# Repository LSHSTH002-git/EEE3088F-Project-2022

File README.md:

# EEE3088F_2022: GROUP 15 LIGHT SENSOR HAT PROJECT

In this guide we will learn to use the LIGHT SENSOR HAT that is used to detect environmental changes and then set off an alarm to alert the onwner about the changes.

This Sensor is primarily designed for farmers that want to monitor their live stock and prevent thieves from stealing them.

# What you will need
1. You will need an STM32f0discovery board

2. Li-Ion battery

3. jumpers

4.  Laptop

5. Micro usb type B male connector

6. STM32CubeIDE

7. Mini USB type A cable

8. The HAT code

9. The HAT pcb Board

# Setting up the System

Insert the Li-ion battery to the battery holder
connect the STM32f0discovery board to your laptop using the Mini USB type A cable
connect the light sensor HAT to your Laptop using Micro usb type B male connector and you should see two LED's light up
run the HAT code on your pc using STM32CubeIDE 
if you cover up the Light sensor HAT, the Blue LED on the STM32f0discovery board should blink

if you stop covering the Light sensor HAT the blue LED should stop blinking.

# License
[Creative Commons Attribution 4.0 International license](https://choosealicense.com/licenses/cc-by-4.0/)

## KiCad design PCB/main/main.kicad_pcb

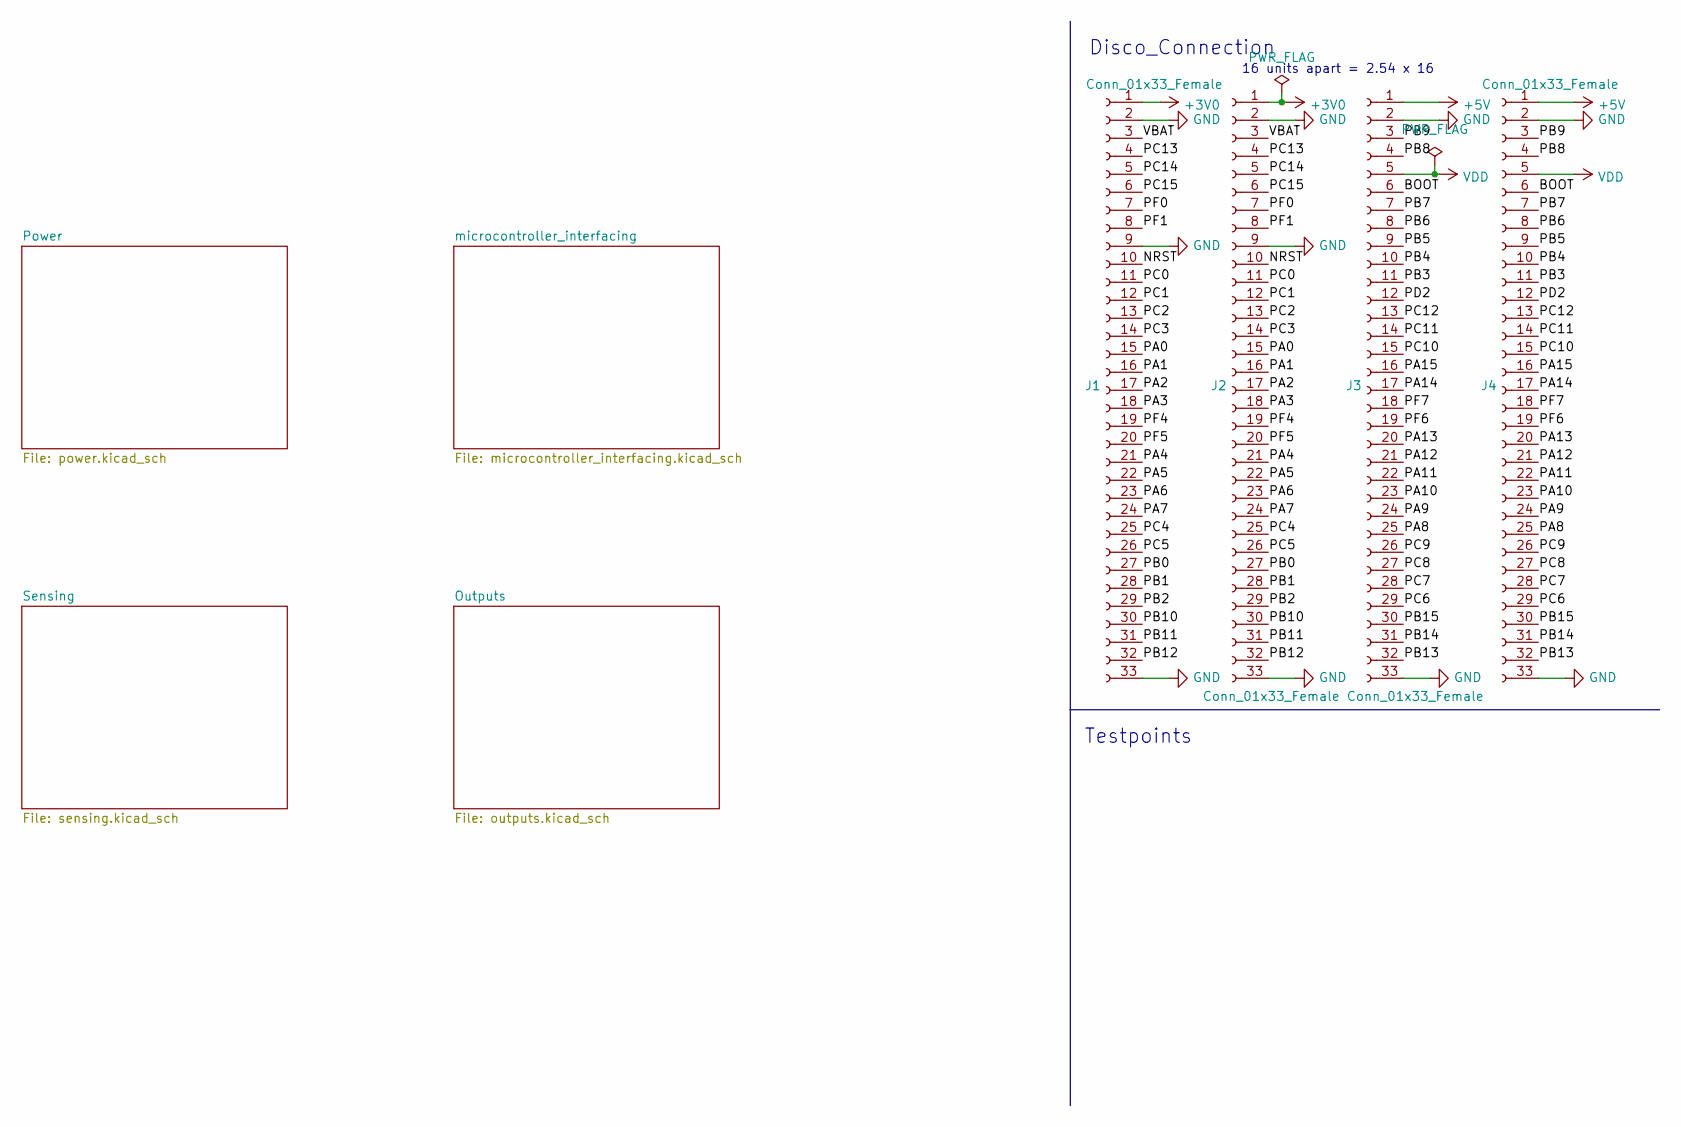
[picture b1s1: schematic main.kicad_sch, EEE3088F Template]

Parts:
J1, J4: Conn_01x33_Female; PinHeader_1x33_P2.54mm_Vertical
J2, J3: Conn_01x33_Female; PinSocket_1x33_P2.54mm_Vertical

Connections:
5V USB: J3.1, J4.1; also elsewhere on the board
+3V0: J1.1, J2.1
/BOOT: J3.6, J4.6
/NRST: J1.10, J2.10
/PA0: J1.15, J2.15
/PA1: J1.16, J2.16
/PA2: J1.17, J2.17
/PA3: J1.18, J2.18
/PA4: J1.21, J2.21
/PA5: J1.22, J2.22
/PA6: J1.23, J2.23
/PA7: J1.24, J2.24
/PA8: J3.25, J4.25
/PA9: J3.24, J4.24
/PA10: J3.23, J4.23
/PA11: J3.22, J4.22
/PA12: J3.21, J4.21
/PA13: J3.20, J4.20
/PA14: J3.17, J4.17
/PA15: J3.16, J4.16
/PB0: J1.27, J2.27
/PB1: J1.28, J2.28
/PB2: J1.29, J2.29
/PB3: J3.11, J4.11
/PB4: J3.10, J4.10
/PB5: J3.9, J4.9
/PB6: J3.8, J4.8
/PB7: J3.7, J4.7
/PB8: J3.4, J4.4
/PB9: J3.3, J4.3
/PB10: J1.30, J2.30
/PB11: J1.31, J2.31
/PB12: J1.32, J2.32
/PB13: J3.32, J4.32
/PB14: J3.31, J4.31
/PB15: J3.30, J4.30
/PC0: J1.11, J2.11
/PC1: J1.12, J2.12
/PC2: J1.13, J2.13
/PC3: J1.14, J2.14
/PC4: J1.25, J2.25
/PC5: J1.26, J2.26
/PC6: J3.29, J4.29
/PC7: J3.28, J4.28
/PC8: J3.27, J4.27
/PC9: J3.26, J4.26
/PC10: J3.15, J4.15
/PC11: J3.14, J4.14
/PC12: J3.13, J4.13
/PC13: J1.4, J2.4
/PC14: J1.5, J2.5
/PC15: J1.6, J2.6
/PD2: J3.12, J4.12
/PF0: J1.7, J2.7
/PF1: J1.8, J2.8
/PF4: J1.19, J2.19
/PF5: J1.20, J2.20
/PF6: J3.19, J4.19
/PF7: J3.18, J4.18
/VBAT: J1.3, J2.3
GND: J1.2, J1.9, J1.33, J2.2, J2.9, J2.33, J3.2, J3.33, J4.2, J4.33; also elsewhere on the board
VDD: J3.5, J4.5

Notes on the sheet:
16 units apart = 2.54 x 16
Disco_Connection
Testpoints

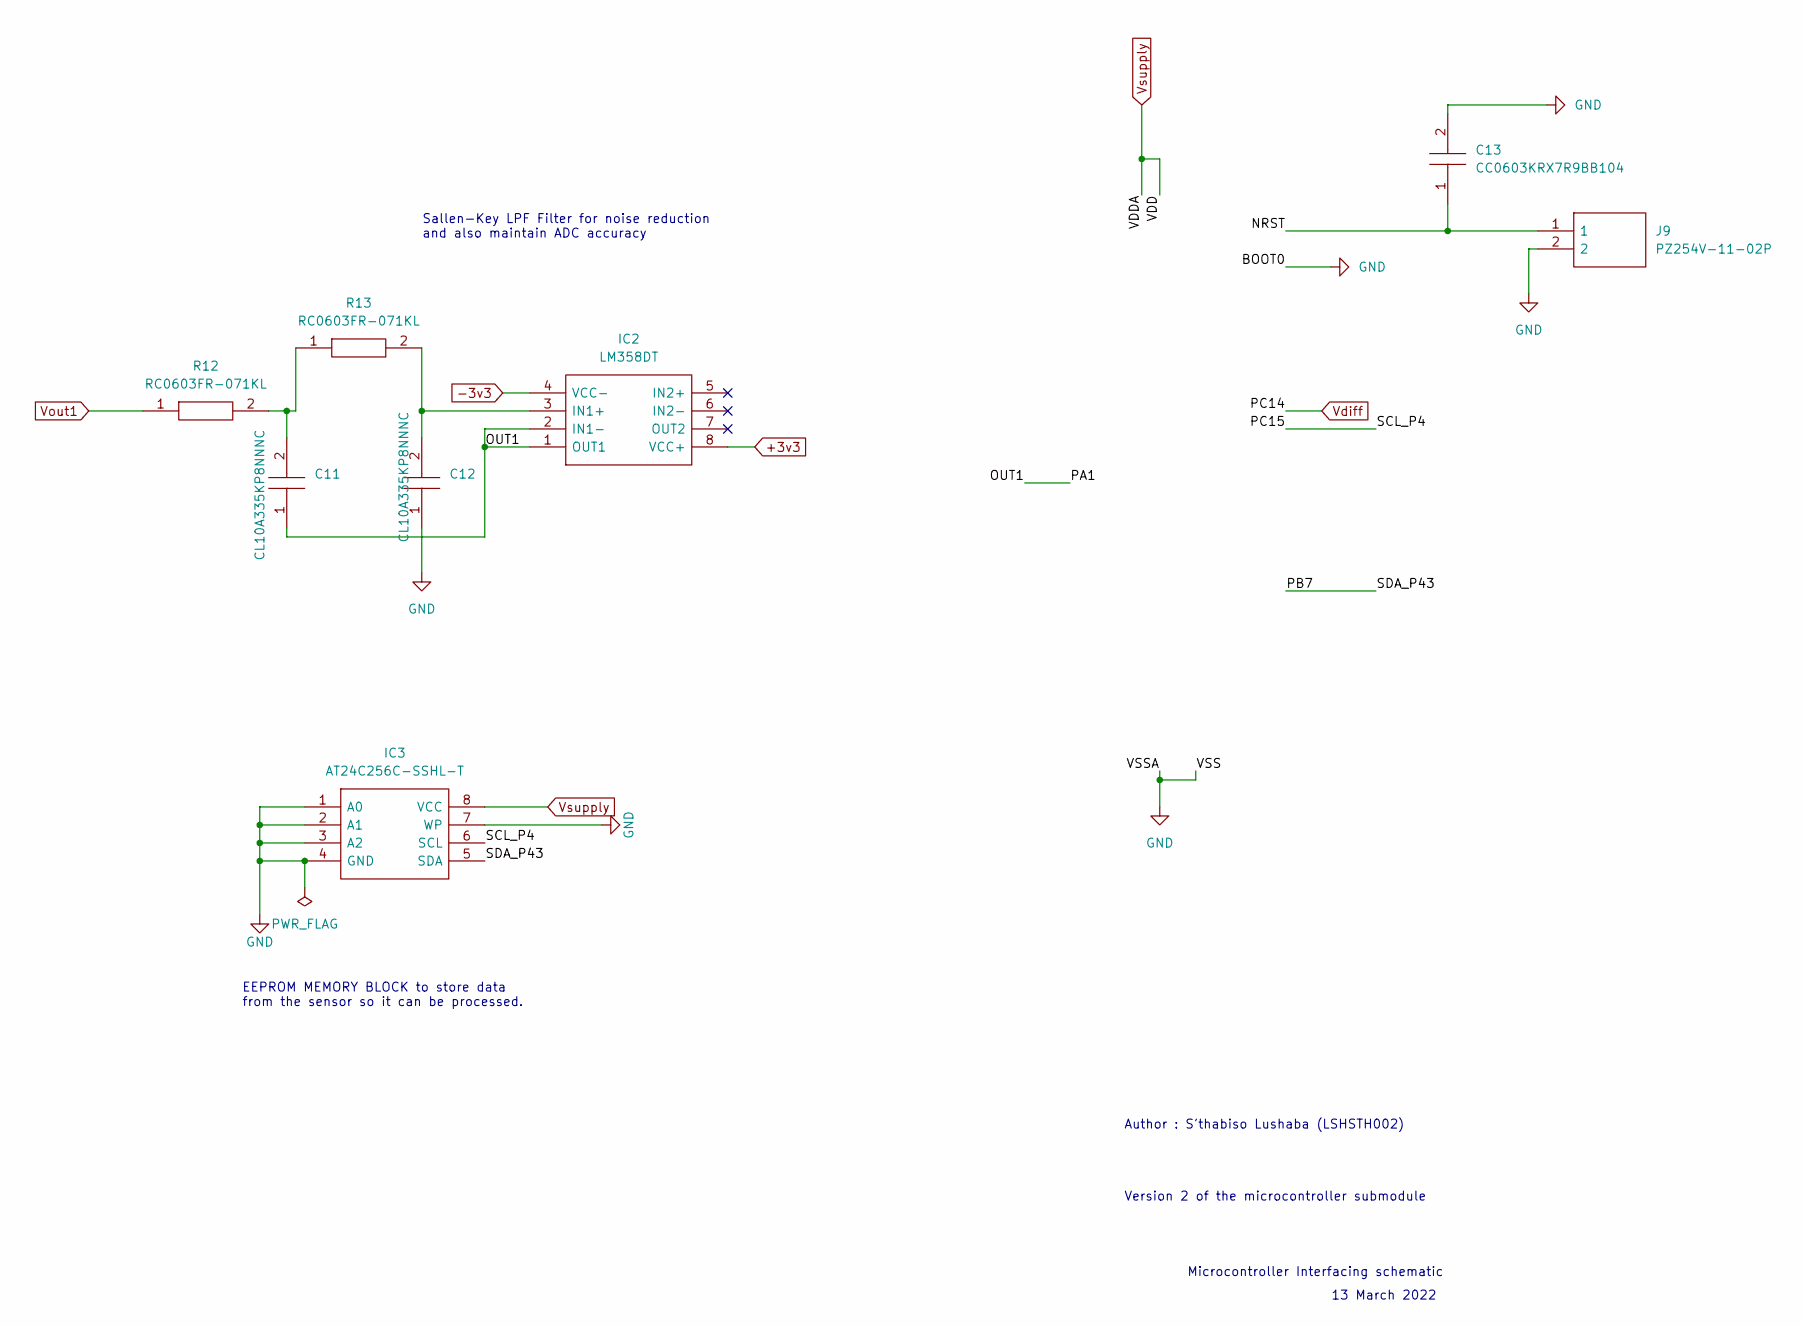
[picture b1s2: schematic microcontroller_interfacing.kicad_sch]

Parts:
C11, C12: CL10A335KP8NNNC; CAPC1608X90N; Manufacturer_Part_Number CL10A335KP8NNNC; Mouser Part Number N/A
C13: CC0603KRX7R9BB104; CAPC1608X90N; Manufacturer_Part_Number CC0603KRX7R9BB104; Mouser Part Number 603-CC603KRX7R9BB104
IC2: LM358DT; SOIC127P600X175-8N; Manufacturer_Part_Number LM358DT; Mouser Part Number 511-LM358DT
IC3: AT24C256C-SSHL-T; SOIC127P600X175-8N; Manufacturer_Part_Number AT24C256C-SSHL-T; Mouser Part Number 556-AT24C256C-SSHL-T
J9: PZ254V-11-02P; HDRV2W64P0X254_1X2_508X250X873P; Manufacturer_Part_Number PZ254V-11-02P; JLCPCB Part Number C492401
R12, R13: RC0603FR-071KL; RESC1608X55N; Manufacturer_Part_Number RC0603FR-071KL; Mouser Part Number 603-RC0603FR-071KL

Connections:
+3v3: IC2.8 (VCC+), IC3.8 (VCC); also elsewhere on the board
-3v3: IC2.4 (VCC-); also elsewhere on the board
/microcontroller_interfacing/NRST: C13.1, J9.1
/microcontroller_interfacing/OUT1: C11.1, IC2.1 (OUT1), IC2.2 (IN1-)
/microcontroller_interfacing/PB7: IC3.5 (SDA)
/microcontroller_interfacing/PC15: IC3.6 (SCL)
GND: C12.1, C13.2, IC3.1 (A0), IC3.2 (A1), IC3.3 (A2), IC3.4 (GND), IC3.7 (WP), J9.2; also elsewhere on the board
unnamed: C11.2, R12.2, R13.1
unnamed: C12.2, IC2.3 (IN1+), R13.2
Vout1: R12.1; also elsewhere on the board

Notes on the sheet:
Author : S'thabiso Lushaba (LSHSTH002)
Version 2 of the microcontroller submodule
Microcontroller Interfacing schematic
13 March 2022
EEPROM MEMORY BLOCK to store data from the sensor so it can be processed.
Sallen-Key LPF Filter for noise reduction and also maintain ADC accuracy

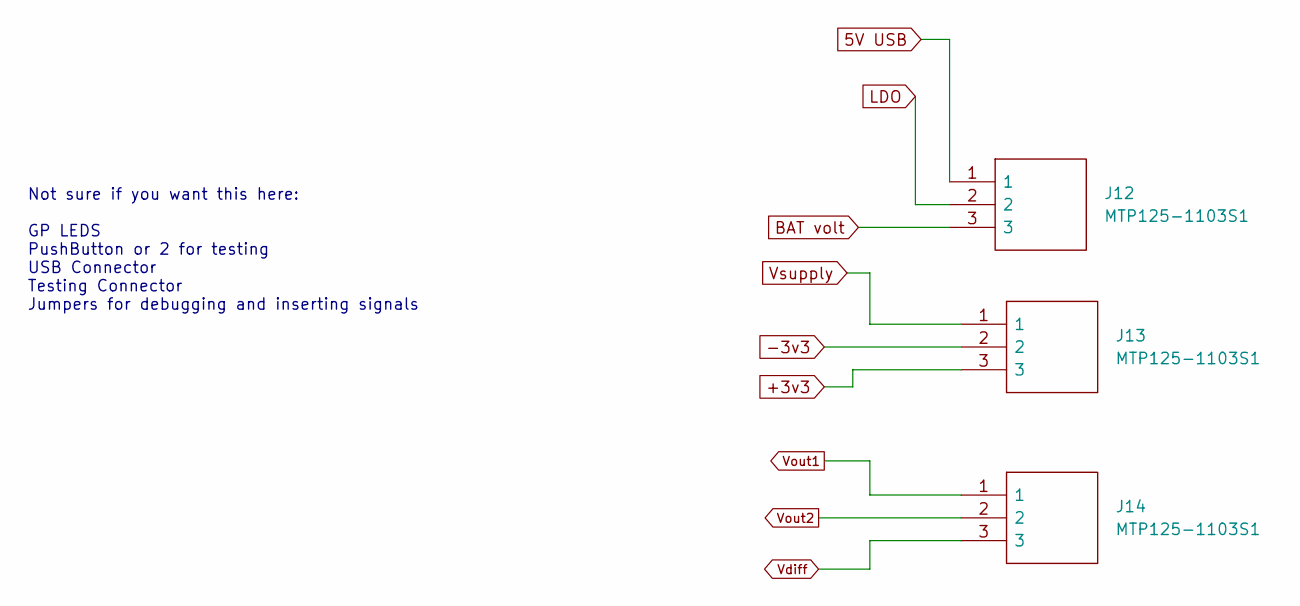
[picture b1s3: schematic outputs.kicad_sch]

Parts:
J12, J13, J14: MTP125-1103S1; HDRV3W64P0X254_1X3_762X250X885P; Manufacturer_Part_Number MTP125-1103S1; LCSC C358685

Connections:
5V USB: J12.1; also elsewhere on the board
+3v3: J13.1, J13.3; also elsewhere on the board
-3v3: J13.2; also elsewhere on the board
BAT volt: J12.3; also elsewhere on the board
LDO: J12.2; also elsewhere on the board
Vdiff: J14.3; also elsewhere on the board
Vout1: J14.1; also elsewhere on the board
Vout2: J14.2; also elsewhere on the board

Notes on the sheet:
Not sure if you want this here: GP LEDS PushButton or 2 for testing USB Connector Testing Connector Jumpers for debugging and inserting signals

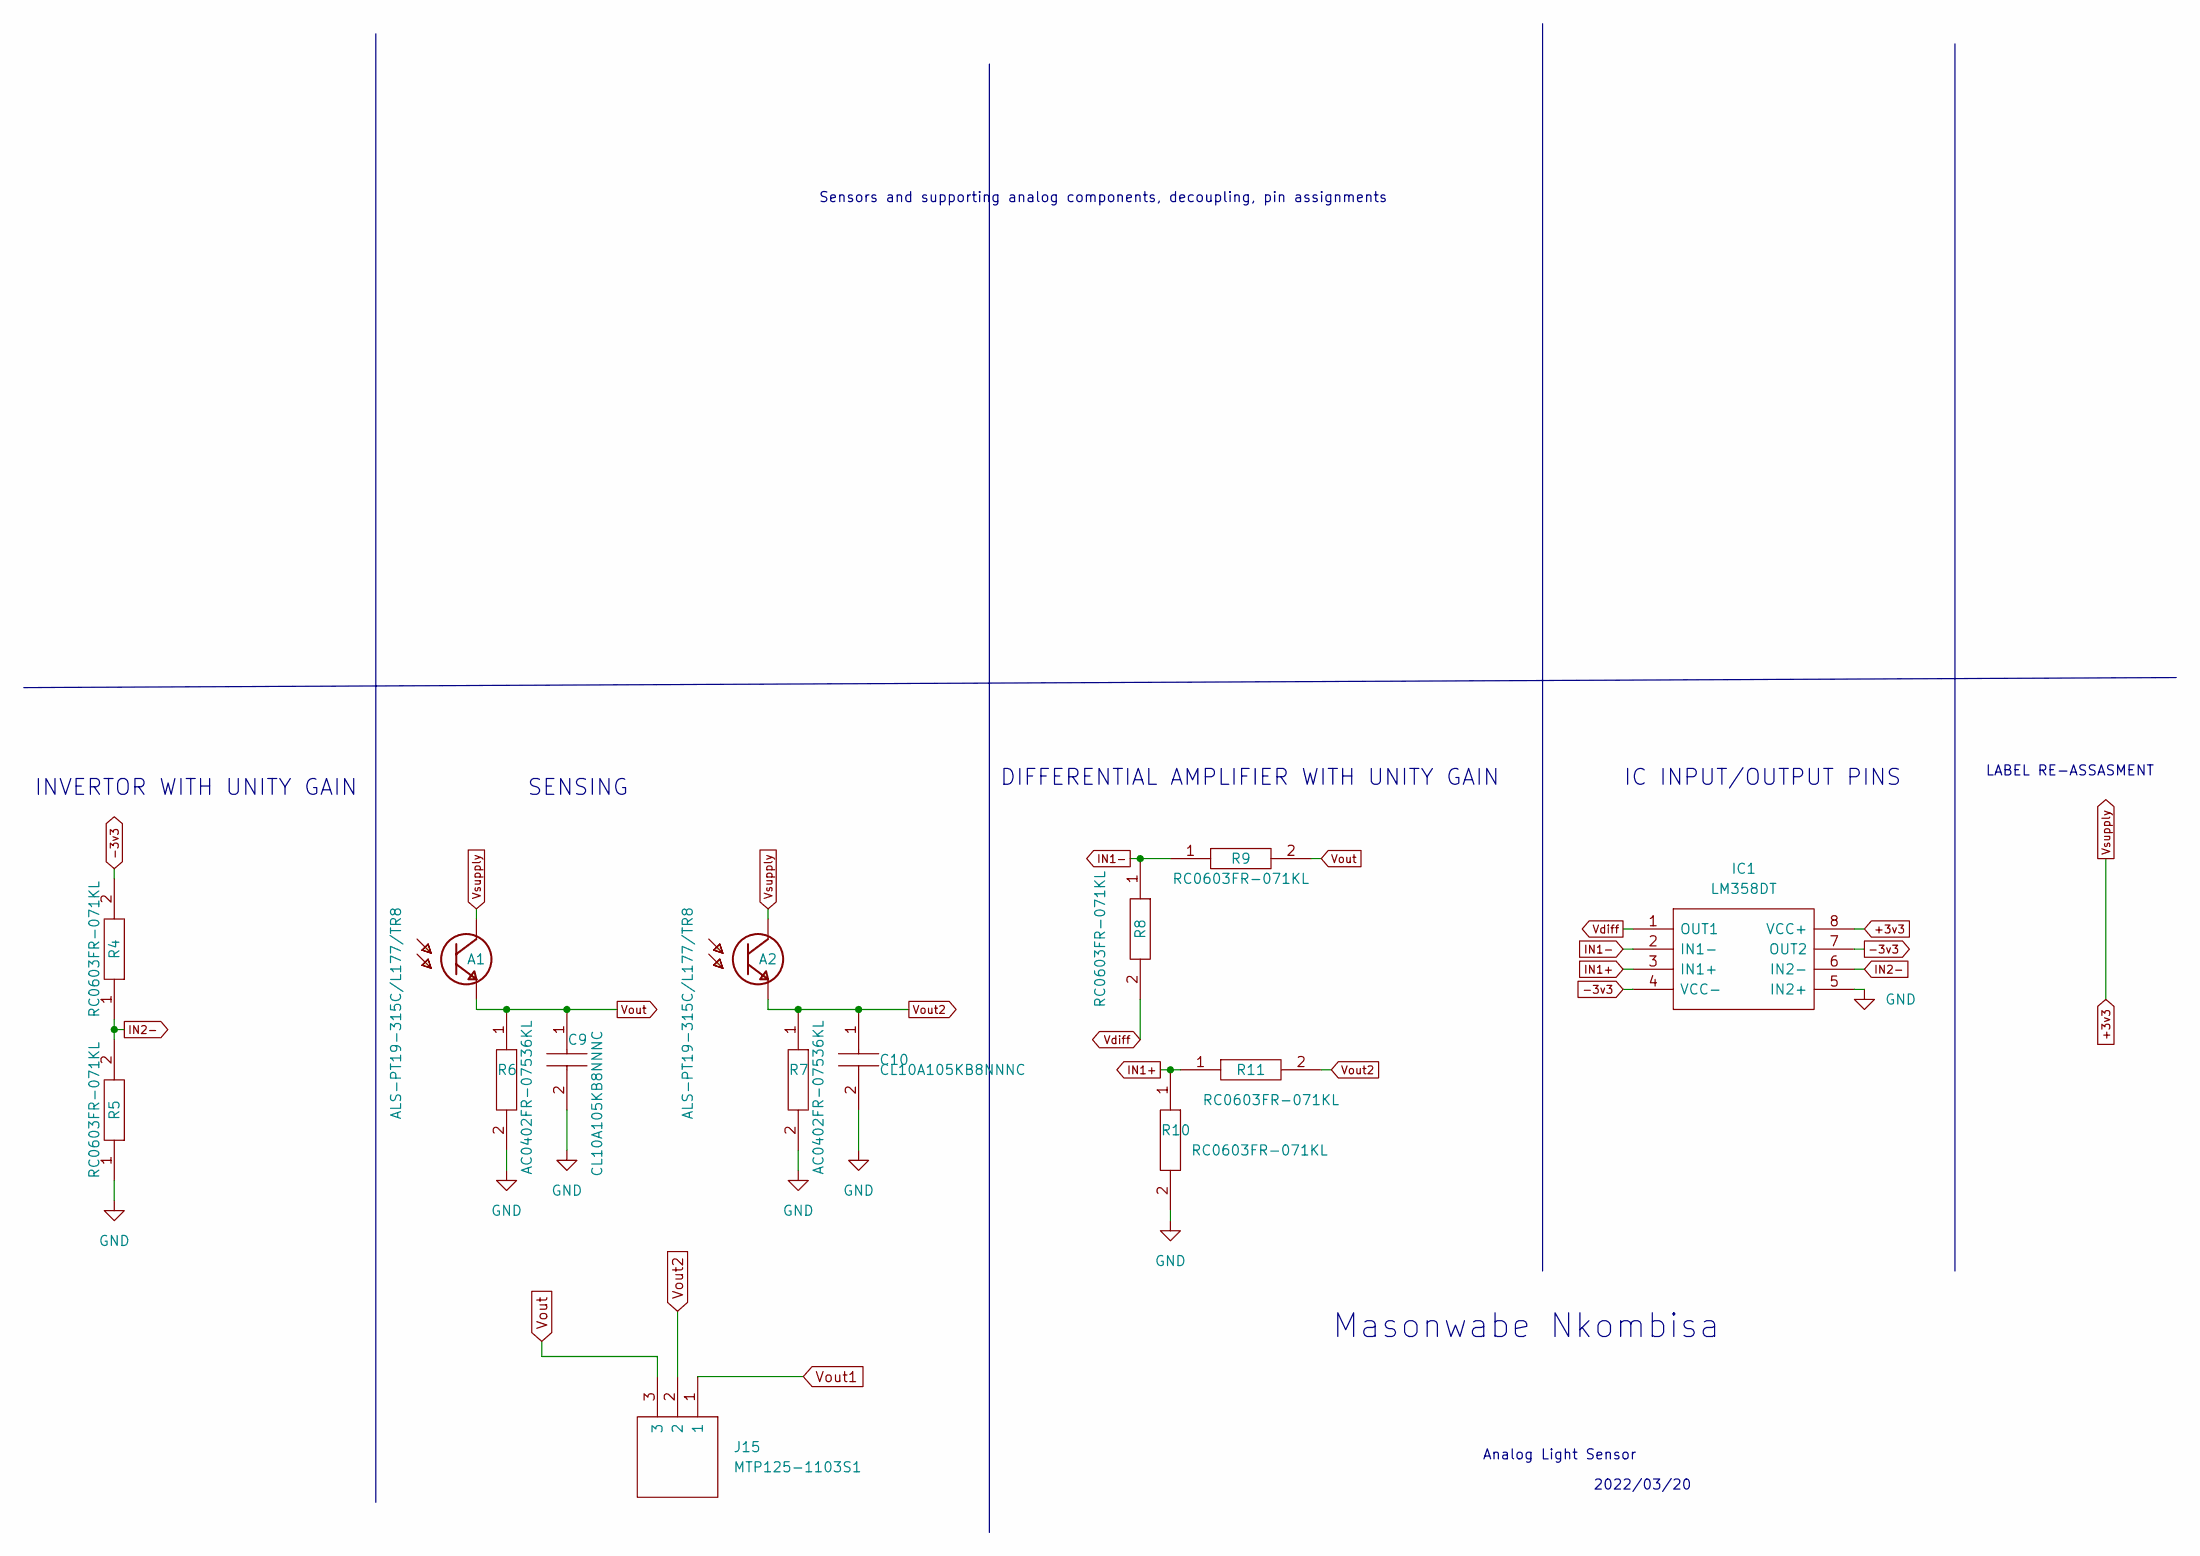
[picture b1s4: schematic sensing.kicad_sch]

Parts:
A1, A2: ALS-PT19-315C/L177/TR8; XDCR_ALS-PT19-315C_L177_TR8; PARTREV 5; LCSC C146233
C9, C10: CL10A105KB8NNNC; CAPC1608X90N; Manufacturer_Part_Number CL10A105KB8NNNC; Mouser Part Number 187-CL10A105KB8NNNC
IC1: LM358DT; SOIC127P600X175-8N; Manufacturer_Part_Number LM358DT; Mouser Part Number 511-LM358DT
J15: MTP125-1103S1; HDRV3W64P0X254_1X3_762X250X885P; Manufacturer_Part_Number MTP125-1103S1; LCSC C358685
R4, R5, R8, R9, R10, R11: RC0603FR-071KL; RESC1608X55N; Manufacturer_Part_Number RC0603FR-071KL; Mouser Part Number 603-RC0603FR-071KL
R6, R7: AC0402FR-07536KL; RESC1005X37N; Manufacturer_Part_Number AC0402FR-07536KL; Mouser Part Number 603-AC0402FR-07536KL

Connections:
+3v3: A1.1, A2.1, IC1.8 (VCC+); also elsewhere on the board
-3v3: IC1.4 (VCC-), IC1.7 (OUT2), R4.2; also elsewhere on the board
GND: C9.2, C10.2, IC1.5 (IN2+), R5.1, R6.2, R7.2, R10.2; also elsewhere on the board
IN1+: IC1.3 (IN1+), R10.1, R11.1
IN1-: IC1.2 (IN1-), R8.1, R9.1
IN2-: IC1.6 (IN2-), R4.1, R5.2
Vdiff: IC1.1 (OUT1), R8.2; also elsewhere on the board
Vout: A1.2, C9.1, J15.3, R6.1, R9.2
Vout1: J15.1; also elsewhere on the board
Vout2: A2.2, C10.1, J15.2, R7.1, R11.2; also elsewhere on the board

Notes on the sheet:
SENSING
LABEL RE-ASSASMENT
IC INPUT/OUTPUT PINS
Sensors and supporting analog components, decoupling, pin assignments
INVERTOR WITH UNITY GAIN
Analog Light Sensor
Masonwabe Nkombisa
DIFFERENTIAL AMPLIFIER WITH UNITY GAIN
2022/03/20

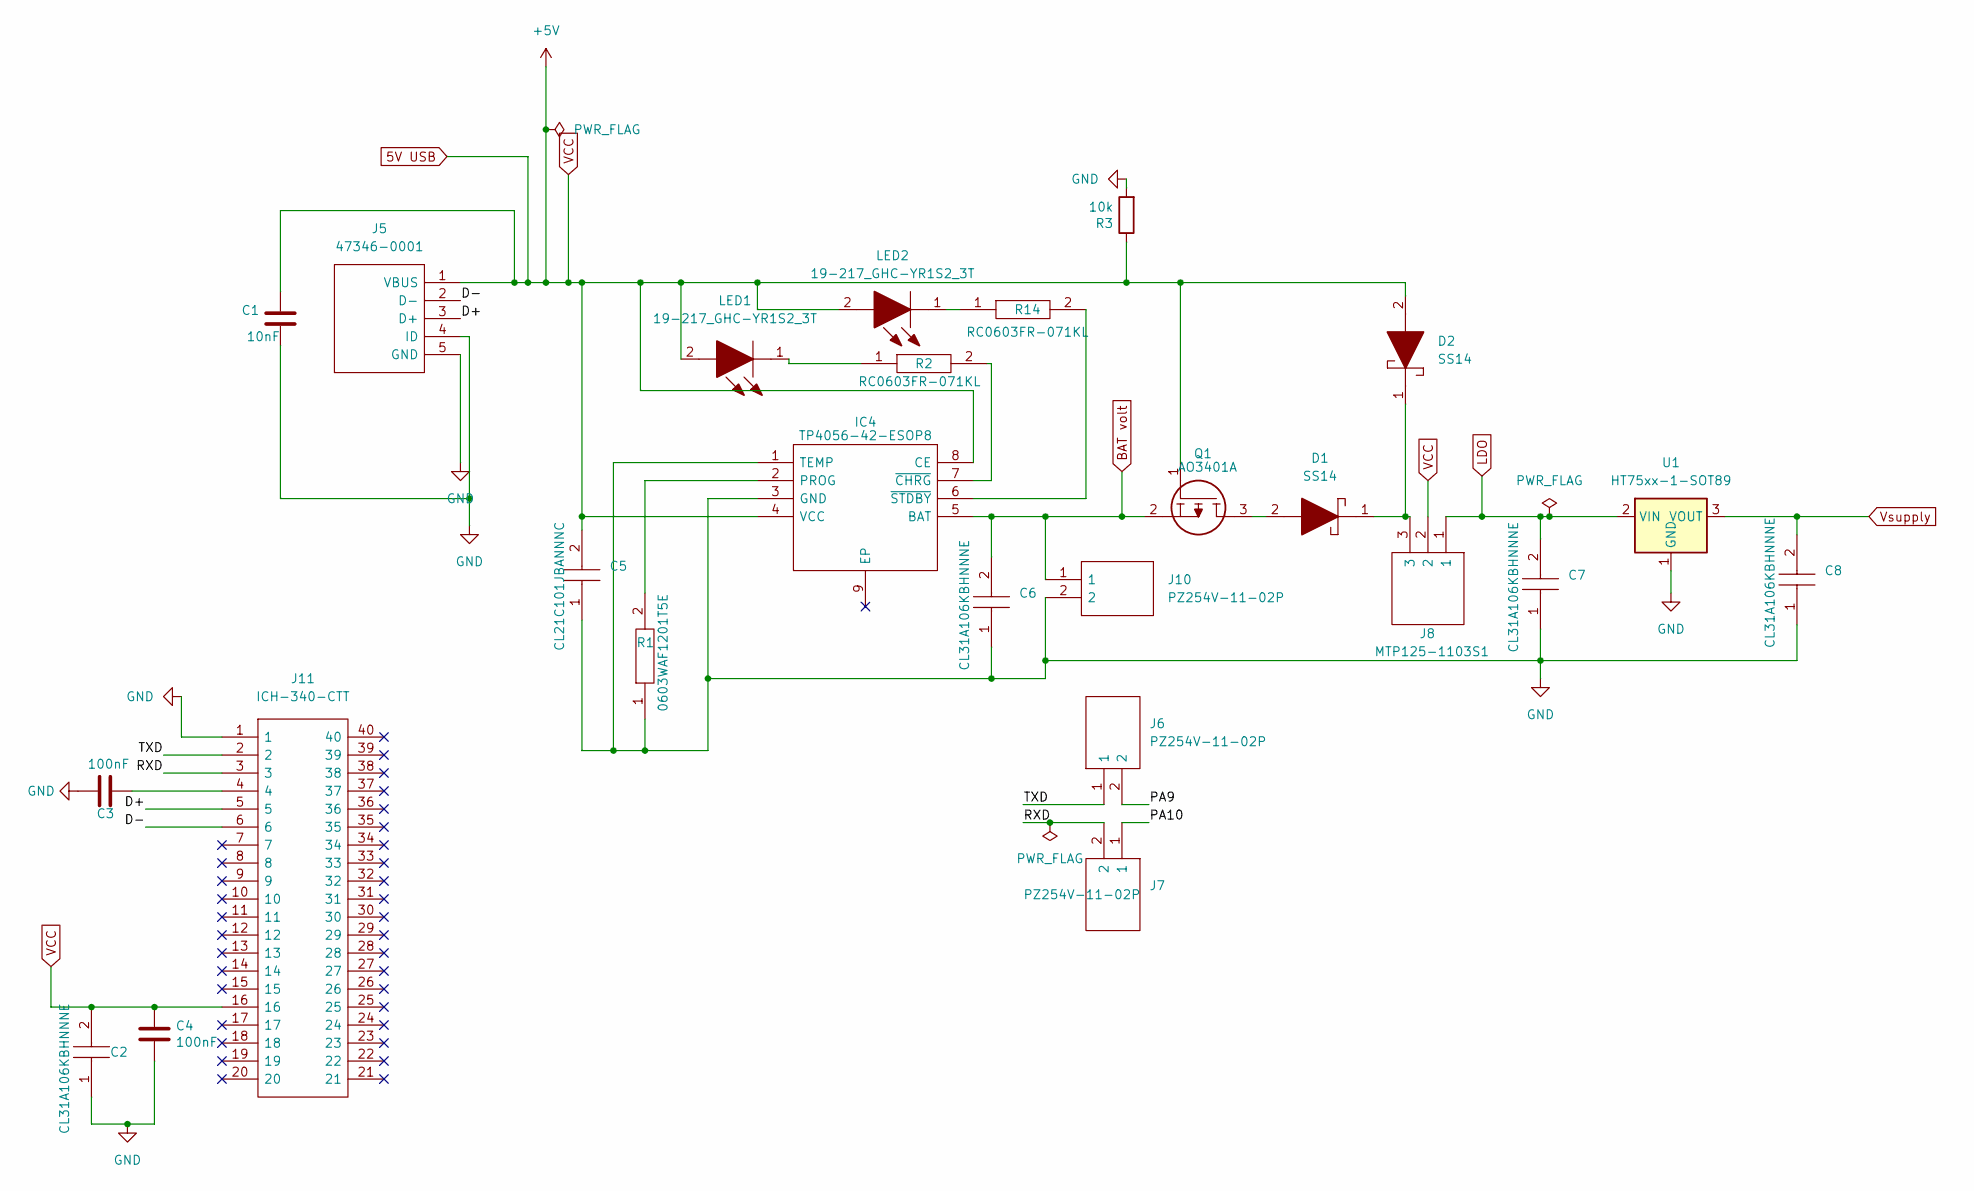
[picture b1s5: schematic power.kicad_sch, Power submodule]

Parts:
C1: 10nF; CAPC1608X90N; JLCPCB Part Number C15195
C2, C6, C7, C8: CL31A106KBHNNNE; CAPC3216X180N; Manufacturer_Part_Number CL31A106KBHNNNE; Mouser Part Number 187-CL31A106KBHNNNE
C3, C4: 100nF; CAPC1608X90N; JLCPCB Part Number C14663
C5: CL21C101JBANNNC; CAPC2012X75N; Manufacturer_Part_Number CL21C101JBANNNC; Mouser Part Number 187-CL21C101JBANNNC
D1, D2: SS14; DIOM5227X270N; Manufacturer_Part_Number SS14; Mouser Part Number 512-SS14
IC4: TP4056-42-ESOP8; SOIC127P600X175-9N; Manufacturer_Part_Number TP4056-42-ESOP8; LCSC C16581
J5: 47346-0001; Manufacturer_Part_Number 47346-0001; Mouser Part Number 538-47346-0001
J6, J7: PZ254V-11-02P; HDRV2W64P0X254_1X2_508X250X873P; Manufacturer_Part_Number PZ254V-11-02P; JLCPCB Part Number C492401
J8: MTP125-1103S1; HDRV3W64P0X254_1X3_762X250X885P; Manufacturer_Part_Number MTP125-1103S1; JLCPCB Part Number C358685
J10: PZ254V-11-02P; HDRV2W64P0X254_1X2_508X250X873P; Manufacturer_Part_Number PZ254V-11-02P; LCSC C492401
J11: ICH-340-CTT; DIPS762W74P254L5080H338Q40N; Manufacturer_Part_Number ICH-340-CTT; LCSC C84681
LED1, LED2: 19-217_GHC-YR1S2_3T; LEDC1608X50N; Manufacturer_Part_Number 19-217/GHC-YR1S2/3T; Mouser Part Number 638-19217GHCYR1S23T
Q1: AO3401A; SOT95P280X125-3N; Manufacturer_Part_Number AO3401A; LCSC C15127
R1: 0603WAF1201T5E; RESC1608X55N; Manufacturer_Part_Number 0603WAF1201T5E; LCSC C22765
R2, R14: RC0603FR-071KL; RESC1608X55N; Manufacturer_Part_Number RC0603FR-071KL; Mouser Part Number 603-RC0603FR-071KL
R3: 10k; RESC1608X55N; JLCPCB Part Number C25804
U1: HT75xx-1-SOT89; SOT-89-3

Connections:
5V USB: C1.2, C2.2, C4.1, C5.2, D2.2, IC4.4 (VCC), IC4.8 (CE), J5.1 (VBUS), J8.2, J11.16, LED1.2, LED2.2, Q1.1, R3.1; also elsewhere on the board
+3v3: C8.2, U1.3 (VOUT); also elsewhere on the board
/Power/D+: J5.3 (D+), J11.5
/Power/D-: J5.2 (D-), J11.6
/Power/PA9: J6.2
/Power/PA10: J7.1
/Power/RXD: J7.2, J11.3
/Power/TXD: J6.1, J11.2
BAT volt: C6.2, IC4.5 (BAT), J10.1, Q1.2; also elsewhere on the board
GND: C1.1, C2.1, C3.2, C4.2, C5.1, C6.1, C7.1, C8.1, IC4.1 (TEMP), IC4.3 (GND), J5.4 (ID), J5.5 (GND), J10.2, J11.1, R1.1, R3.2, U1.1 (GND); also elsewhere on the board
LDO: C7.2, J8.1, U1.2 (VIN); also elsewhere on the board
unnamed: C3.1, J11.4
unnamed: D1.1, D2.1, J8.3
unnamed: D1.2, Q1.3
unnamed: IC4.2 (PROG), R1.2
unnamed: IC4.6 (~STDBY), R14.2
unnamed: IC4.7 (~CHRG), R2.2
unnamed: LED1.1, R2.1
unnamed: LED2.1, R14.1

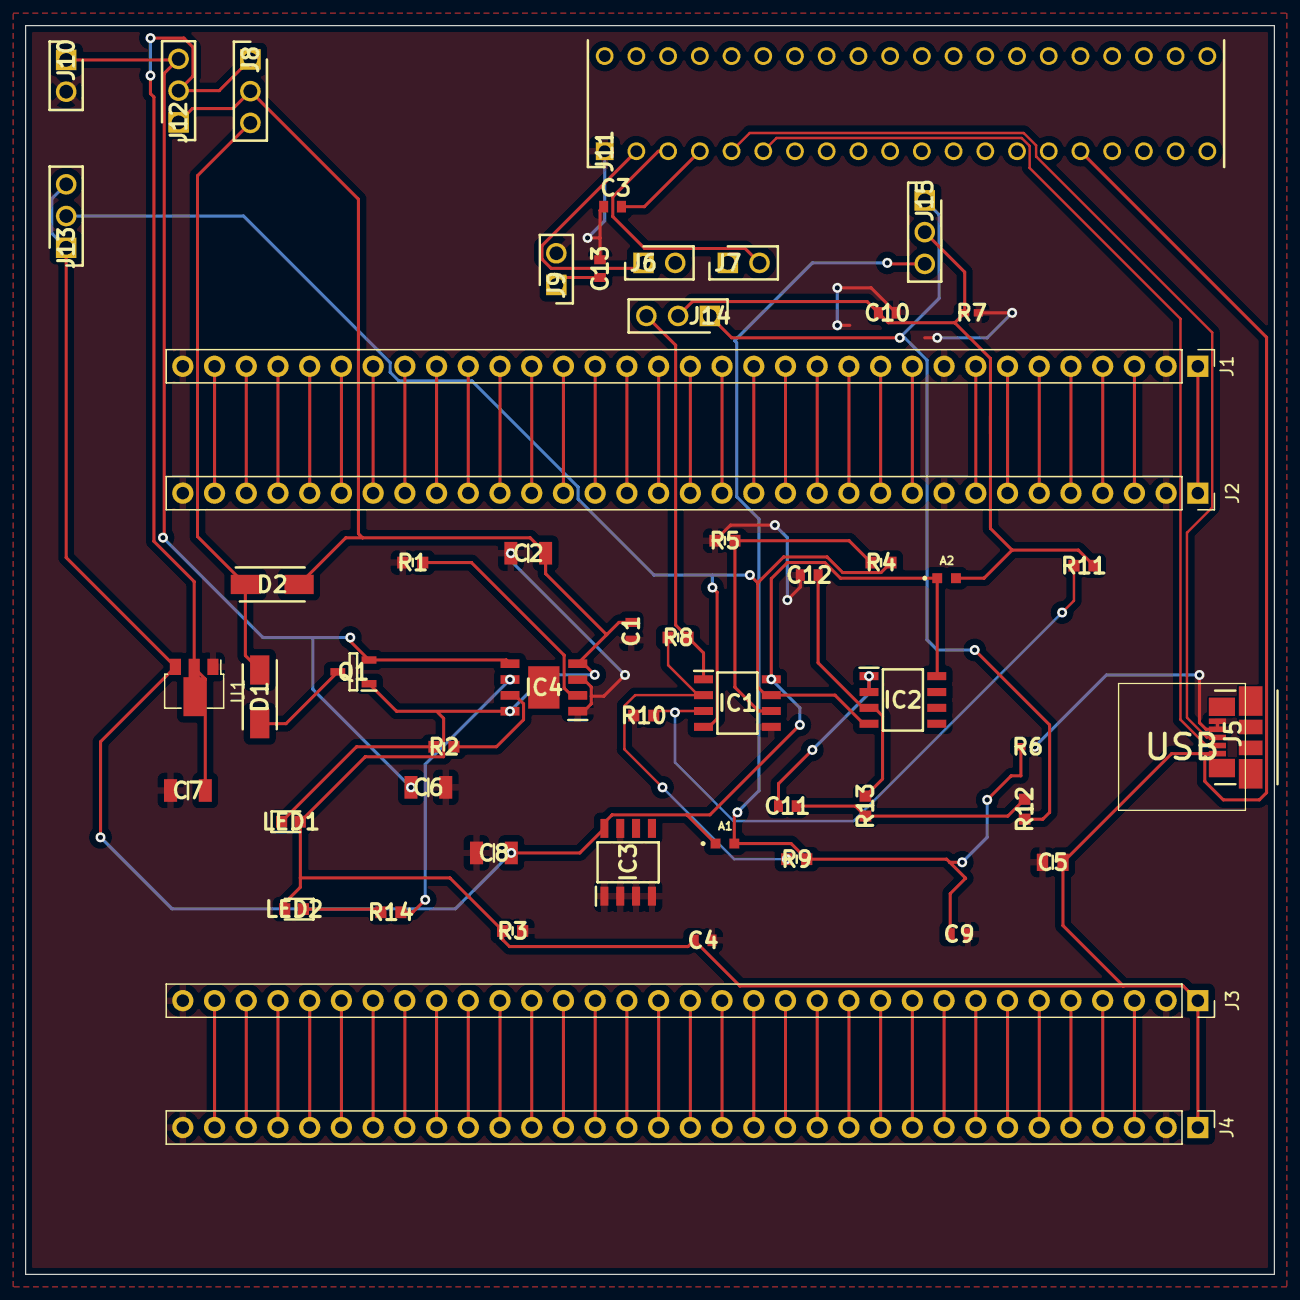
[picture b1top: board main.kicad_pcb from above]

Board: 2 copper layers, 100.0 x 100.0 mm, 54 parts (0 on the bottom side), 89 nets.

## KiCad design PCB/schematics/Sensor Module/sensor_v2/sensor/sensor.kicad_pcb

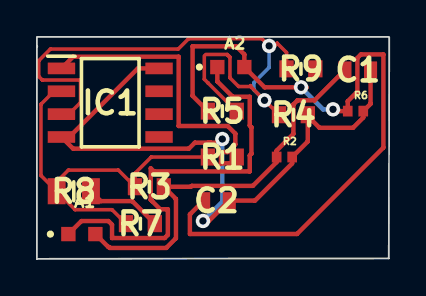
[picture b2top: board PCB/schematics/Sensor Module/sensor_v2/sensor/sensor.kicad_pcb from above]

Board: 2 copper layers, 19.6 x 12.3 mm, 14 parts (0 on the bottom side), 8 nets.

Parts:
A1, A2: ALS-PT19-315C/L177/TR8; XDCR_ALS-PT19-315C_L177_TR8
C1, C2: CL10A105KB8NNNC; CAPC1608X90N
IC1: LM358DT; SOIC127P600X175-8N
R1, R3, R4, R5, R7: RC0603FR-071KL; RESC1608X55N
R2, R6: AC0402FR-07536KL; RESC1005X37N
R8: CR0805-FX-5110ELF; RESC2012X60N
R9: RC0603JR-0710KL; RESC1608X55N

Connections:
3v3: A1.1, A2.1
+3v3: C1.2, C2.2, IC1.4 (VCC-), IC1.8 (VCC+), R2.2, R4.2, R6.2
+5v: R7.2, R8.2
IN1+: IC1.3 (IN1+), R4.1, R5.1, R9.1
IN1-: IC1.2 (IN1-), R1.1, R3.1, R7.1, R8.1
Vdiff: IC1.1 (OUT1), R1.2
Vout1: A1.2, C1.1, R2.1, R3.2
Vout2: A2.2, C2.1, R5.2, R6.1

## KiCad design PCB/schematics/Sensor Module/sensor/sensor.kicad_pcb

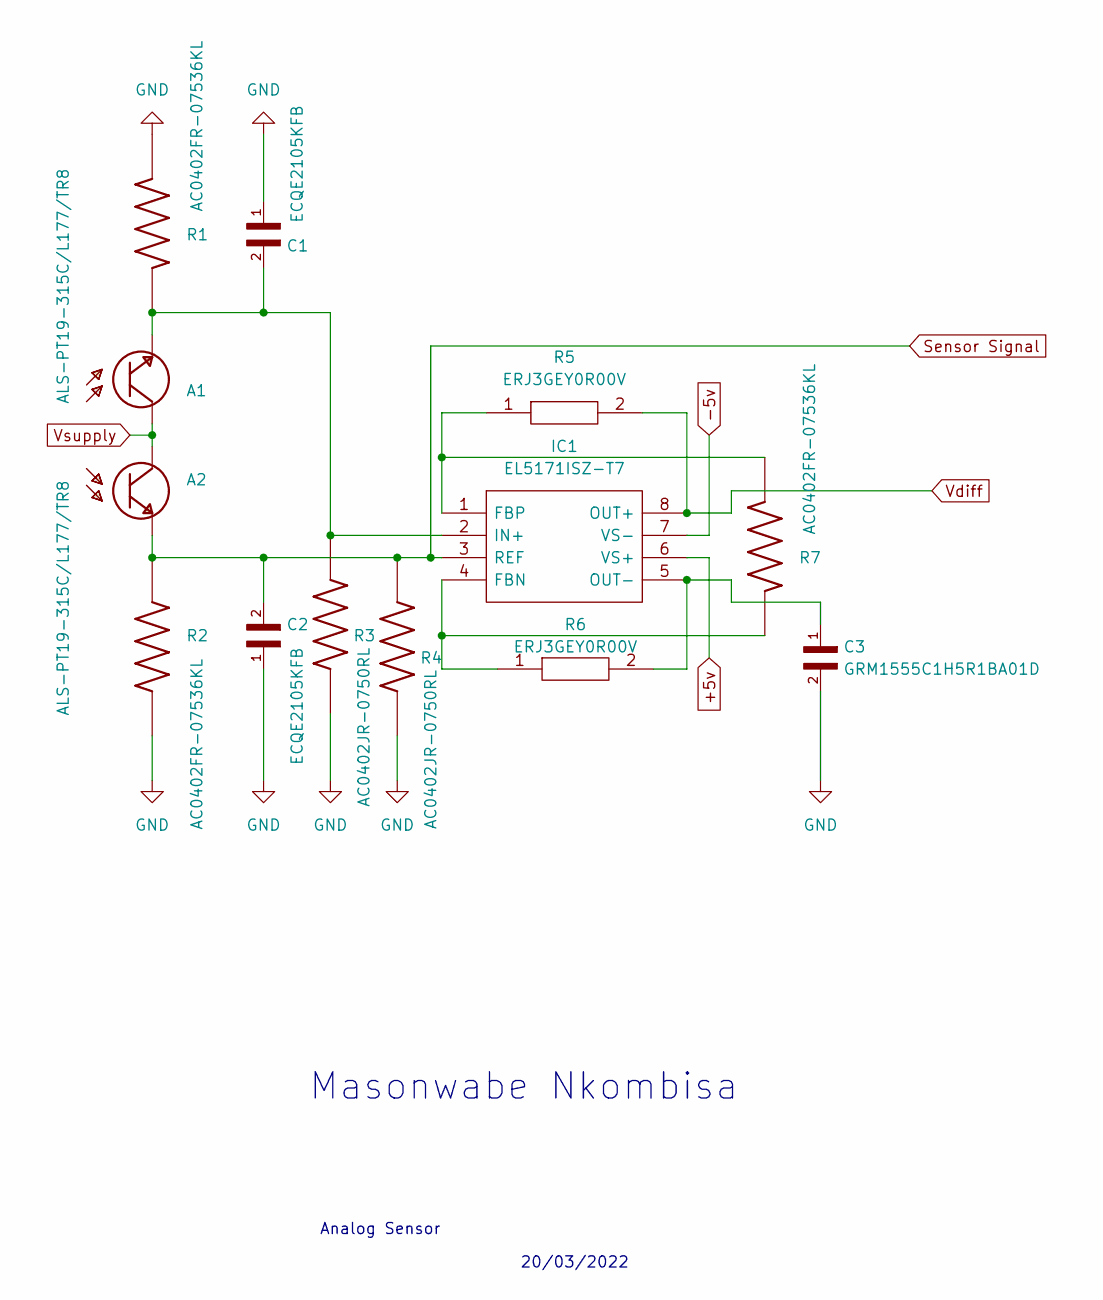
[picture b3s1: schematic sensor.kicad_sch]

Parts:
A1, A2: ALS-PT19-315C/L177/TR8; XDCR_ALS-PT19-315C_L177_TR8; PARTREV 5; LCSC C146233
C1, C2: ECQE2105KFB; CAPRR1000W80L1850T740H2000; PARTREV 11-Oct-17; LCSC C178438
C3: GRM1555C1H5R1BA01D; CAPC1005X55N; LCSC C415534
IC1: EL5171ISZ-T7; SOIC127P600X175-8N; Manufacturer_Part_Number EL5171ISZ-T7; Mouser Part Number 968-EL5171ISZ-T7
R1, R2, R7: AC0402FR-07536KL; RESC1005X37N; LCSC C144748
R3, R4: AC0402JR-0750RL; RESC1005X37N; LCSC C227387
R5, R6: ERJ3GEY0R00V; ERJ3EKF1000V; Manufacturer_Part_Number ERJ3GEY0R00V; LCSC C122704

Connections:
+5v: IC1.6 (VS+)
-5v: IC1.7 (VS-)
GND: C1.1, C2.1, C3.2, R1.1, R2.1, R3.1, R4.1
unnamed: A1.2, C1.2, IC1.2 (IN+), R1.2, R3.2
unnamed: C3.1, IC1.5 (OUT-), R6.2
unnamed: IC1.1 (FBP), R5.1, R7.1
unnamed: IC1.4 (FBN), R6.1, R7.2
Sensor Signal: A2.2, C2.2, IC1.3 (REF), R2.2, R4.2
Vdiff: IC1.8 (OUT+), R5.2
Vsupply: A1.1, A2.1

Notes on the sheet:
20/03/2022
Masonwabe Nkombisa
Analog Sensor

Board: 2 copper layers, 13 parts (0 on the bottom side), 8 nets, no tracks yet.

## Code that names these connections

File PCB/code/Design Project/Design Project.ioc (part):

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Mcu.Name=STM32F051R8Tx
Mcu.Package=LQFP64
Mcu.UserName=STM32F051R8Tx
PA1.Signal=GPIO_Analog
PA10.Mode=Asynchronous
PA10.Signal=USART1_RX
PA9.Mode=Asynchronous
PA9.Signal=USART1_TX
PB7.Mode=I2C
PB7.Signal=I2C1_SDA
PB8.Mode=I2C
PB8.Signal=I2C1_SCL
PC14-OSC32_IN.Signal=GPIO_Analog
PC8.Signal=GPIO_Output
board=custom

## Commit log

2022-03-04 Bill Of Material Microcontroller Interface
2022-03-04 Add files via upload
    added Bill of Materials for power submodule
2022-03-10 1st commit
2022-03-10 Microcontroller Bill Of Material Version 1
2022-03-10 Power_submodele_BOM v1
2022-03-10 power schematic v1
2022-03-11 Microcontroller Submodule Version 1
2022-03-11 My first commit
2022-03-12 Analog sensor BOM
2022-03-12 microcontroller interfacing submodule version 2
2022-03-12 removed the old bill of material
2022-03-12 updated microcontroller schematic
2022-03-12 power submodule BOM version2
2022-03-12 4TH WEEK, CHANGES FOR SENSING
2022-03-12 4TH WEEK, CHANGES FOR SENSING INCLUDING THE KICAD ERC TEST FILE
2022-03-12 added FTDIto the schematic
2022-03-20 updated bill of material Microcontroller
2022-03-20 updated power schematic
2022-03-20 added library for power
2022-03-20 updated power BOM
2022-03-20 moved power schematics to main
2022-03-20 updated microcontroller bill of material
2022-03-20 Week 5 submission, with improved version of the sensor
2022-03-20 Week 5 submission, with analog sensor.
2022-03-20 updated bill of material
2022-03-20 Week 5 submission, with analog sensor with pcb updated
2022-03-20 updated microcontroller footprints and that..
2022-03-21 assigned new footprints
2022-03-21 added power library
2022-03-21 modified power lib
2022-03-21 Sensing module combined with main module
2022-03-21 power and microcontroller updated
2022-03-21 changes made to all
2022-03-21 microcontroller files
2022-03-21 sensor bill of material
2022-03-21 power module
2022-03-21 changed USB MICRO
2022-03-21 modified power library
2022-03-21 updated stuff
2022-03-21 git main schematics updated
2022-03-21 changed made on PCD
2022-03-21 PCB geber files
2022-03-21 PDF of total production costs
2022-03-22 wired the pcb a bit
2022-03-22 main with 0 DRC errors
2022-03-22 Update on pcb
2022-03-23 pcb with no errors, violations
2022-04-04 main modified by masonwabe
2022-04-04 updated PCB with mount holes
2022-04-05 latest changes
2022-04-05 updated power BOM and total cost
2022-04-06 Modified pcb to reduced the gnd and 3.3v lines
2022-04-08 added test points and jumpers
2022-04-08 added more test points
2022-04-08 pcb update
2022-04-08 gerber files and dat
2022-04-11 added pos file and zip file to save BOM
2022-04-11 Added position files
2022-04-11 gerber files final
2022-04-12 created BOM
2022-04-16 modified power schematic
2022-04-16 new PCB
2022-04-16 new footprints
2022-04-16 generated Gerbers
2022-04-16 removed old files
2022-04-17 changed power schematic
2022-04-17 NEW PCB ADDED
2022-04-22 Added sensor sch to the schematics folder
2022-04-23 generated new files
2022-04-25 created new BOM,POS and Gerbers
2022-05-09 dajksh
2022-05-23 checking if readmefile updated
2022-05-23 readmefile updated
2022-05-23 Code Structure Q1
2022-05-23 Updated Code Structure
2022-05-23 Add CONTRIBUTING
2022-05-23 Adding pictures to the README.md file
2022-05-23 Updated Code Structure Diagrams
2022-05-23 added code reference document
2022-05-23 last commit from me
2022-05-23 editted CONTRIBUTING.md file
